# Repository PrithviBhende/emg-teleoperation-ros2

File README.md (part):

# Surface EMG-Based Hand Movement Recognition and Virtual Robotic Hand Teleoperation

An end-to-end cyber-physical pipeline integrating **surface electromyography (sEMG)** bio-signal acquisition, automated **computer vision ground-truth labelling**, **machine learning classification** (evaluating 21 feature-classifier combinations across sets A–G with LDA, SVM, and KNN), and real-time low-latency teleoperation of a 17-DOF **InMoov humanoid robotic hand** in **ROS 2 Humble** and **Gazebo Classic**.

---

## Table of Contents
1. [System Architecture & Dataflow](#1-system-architecture--dataflow)
2. [Hardware Devices & Sensor Configuration](#2-hardware-devices--sensor-configuration)
3. [Custom 6-Channel sEMG Acquisition Hardware (ADS1296)](#3-custom-6-channel-semg-acquisition-hardware-ads1296)
4. [Interactive Graphical User Interface (GUI) Walkthrough](#4-interactive-graphical-user-interface-gui-walkthrough)
5. [Signal Processing, Feature Sets (A to G) & ML Models](#5-signal-processing-feature-sets-a-to-g--ml-models)
6. [ROS 2 & Gazebo Virtual Robotic Hand Simulation](#6-ros-2--gazebo-virtual-robotic-hand-simulation)
7. [Experimental Results & Benchmark Performance](#7-experimental-results--benchmark-performance)
   - [Master Benchmark Evaluation Table](#master-benchmark-evaluation-table)
   - [Waveform Characteristics (All 8 Gestures)](#waveform-characteristics)
   - [Training Results & Graphical Representations (`results/training_results/`)](#-training-results--graphical-representations-directory)
8. [Step-by-Step Guide: How to Make It Work](#8-step-by-step-guide-how-to-make-it-work)
9. [Relative Repositories, Documentation & References](#9-relative-repositories-documentation--references)

---

## 1. System Architecture & Dataflow

The system bridges biological neuromuscular intent to virtual robotic actuation through a synchronized multi-stage pipeline:

```mermaid
flowchart LR
    A["Forearm Muscle Flexion"] --> B["sEMG Electrodes + BioAmp Shield"]
    B --> C["Arduino Due (2 kHz 12-bit ADC)"]
    C -->|"Binary Stream: EMG1 Packet + CRC32"| D["Windows Desktop GUI Application"]
    E["Monocular RGB Webcam"] -->|"MediaPipe Hand Landmarker"| D
    D --> F["Windowing (250 ms, 50 ms hop)<br/>Feature Extraction (Sets A–G)"]
    F --> G["Classifier Inference<br/>(LDA / SVM / KNN)"]
    G --> H["Majority Vote & Rejection Gate<br/>(Threshold >= 60%)"]
    H -->|"TCP Socket (localhost:9996)"| I["WSL 2: ros2_gazebo_server"]
    I -->|"/finger_position_controller/commands"| J["Gazebo: InMoov 17-DOF Hand"]
```

1. **Neuromuscular Sensing**: Surface electrical potentials generated during muscle contractions on the forearm are captured by Ag/AgCl differential electrodes.
2. **Signal Conditioning & Digitization**: The analogue signal is band-pass filtered (72–720 Hz) and amplified by an Upside Down Labs Muscle BioAmp Shield v0.3, then sampled by an Arduino Due 12-bit ADC at a continuous **2,000 Hz**.
3. **High-Speed Serial Streaming**: Data is packed into custom framed binary packets (`EMG1` protocol, 26-byte header, 32-sample payload, CRC32 checksum) and sent via Native USB serial to the Windows host.
4. **Automated Vision-Guided Labeling**: A synchronized camera feed processes hand gestures using Google MediaPipe Hand Landmarker, computing 3D geometric finger joint angles to generate objective reference labels during training.
5. **Feature Extraction & Multi-Model Inference**: Overlapping 250 ms windows (50 ms hop) extract time-domain and time-frequency spectral features (Sets A through G). Predictions are computed across Linear Discriminant Analysis (LDA), Support Vector Machine (SVM), and K-Nearest Neighbors (KNN).
6. **Cross-Platform Teleoperation Bridge**: Accepted gesture commands are transmitted over a high-speed TCP socket (`localhost:9996`) to a ROS 2 bridge node running inside WSL 2 Ubuntu 22.04.
7. **Virtual Actuation**: The ROS 2 bridge node translates gesture tokens into 17 target joint angles published to `/finger_position_controller/commands`, driving the simulated InMoov robotic hand in Gazebo Classic in real time.

---

## 2. Hardware Devices & Sensor Configuration

### Single-Channel Benchmarking Platform
* **Microcontroller**: Arduino Due featuring an Atmel/Microchip SAM3X8E 32-bit ARM Cortex-M3 processor clocked at 84 MHz.
  * Internal 12-bit Analog-to-Digital Converter (`0–4095` counts).
  * Hardware timer interrupt-driven sampling at exact 2,000 samples/second.
  * Native USB CDC communication at full bus speed (exceeding standard 115200 baud UART bandwidth constraints).
* **Bio-Potential Amplifier**: Upside Down Labs Muscle BioAmp Shield v0.3.
  * Analogue front-end instrumentation amplifier with differential gain $A_v \approx 1000$.
  * Analogue bandpass filter: $72\text{ Hz} - 720\text{ Hz}$.
  * Power supply: 5.0 V rail derived from Arduino Due 5V pin.
* **Safety & Voltage Conditioning**:
  * **Critical Electrical Constraint**: The Arduino Due SAM3X8E ADC pin A0 is strictly 3.3 V tolerant (`0 – 3.3 V`). Feeding raw 5 V output from the shield risks permanent pin damage.
  * A passive voltage divider and protection network ensures voltage peaks never exceed the 3.3 V threshold under full muscle contraction.
* **Electrodes**:
  * Standard clinical disposable Ag/AgCl hydrogel pre-gelled surface electrodes (24 mm diameter).
  * Placed in a bipolar arrangement along the muscle belly of the *Flexor Digitorum Superficialis* (FDS) and *Flexor Carpi Radialis* (FCR) on the anterior forearm.
  * Ground / reference electrode placed on a neutral bony landmark: the olecranon process of the elbow.

---

## 3. Custom 6-Channel sEMG Acquisition Hardware (ADS1296)

To scale from single-channel discrimination to simultaneous multi-finger gesture decoding, a dedicated **6-channel bio-potential acquisition carrier board** was designed in KiCad.

### Key Architectural Specifications
* **Analog Front-End (AFE)**: Texas Instruments **ADS1296** (6-channel, 24-bit simultaneous sampling delta-sigma ADC with programmable gain amplifiers, PGA = 1 to 12).
* **Sampling Throughput**: Target 4,000 samples/second per channel across 6 simultaneous differential channels (24-bit frame = 21 bytes per sample, 84 kB/s raw stream).
* **Host Controller**: Removable **Waveshare ESP32-S3-Tiny** dual-core Xtensa LX7 MCU mounted via dual 1x9 female header sockets (2.54 mm pitch, 15.24 mm row spacing).
* **Board Dimensions**: 100 mm x 80 mm, 4-layer FR4 stackup, 1.6 mm thickness.
* **Power Supply**:
  * Battery branch input: 5.0 V regulated via J1.
  * Analog rail: Texas Instruments **LP5907** ultra-low-noise 3.0 V linear regulator (sub-10 µV RMS output noise, 250 mA rating).
  * Digital rail: 3.3 V supplied by the ESP32-S3 module.

### PCB Layer Stackup
| Layer | Name | Type | Description |
|:---:|:---|:---:|:---|
| **L1** | F.Cu | Top Signal | Surface-mount components (109 footprints), high-frequency SPI bus, RF antenna keepout |
| **L2** | In1.Cu | Ground Plane | Solid, uninterrupted GND reference return plane across entire board |
| **L3** | In2.Cu | Power Plane | Clean analog AVDD (3.0 V) copper pour, isolated digital power routing |
| **L4** | B.Cu | Bottom Signal | Critical return paths, plus underside decoupling capacitors (C14, C27, R21, C23) |

### Hierarchical Schematic Architecture

The KiCad project is structured across seven modular hierarchical sheets:

#### Sheet 01: Root Hierarchical Architecture
Orchestrates global inter-sheet busses, power rails, differential analog input channels, SPI command lines, and ground isolation.

#### Sheet 02: Power Management & Low-Noise Decoupling
Houses the TI LP5907 3.0V low-dropout regulator, bulk input tantalum capacitors, LC filter beads, and localized ceramic decoupling capacitors ($10\text{ }\mu\text{F} \parallel 0.1\text{ }\mu\text{F}$) positioned immediately adjacent to power pins.

#### Sheet 03: ADS1296 Bio-Potential Core & Pin Mapping
Contains the central 64-pin TQFP ADS1296 analog front-end, internal reference generation ($V_{REF} = 2.42\text{ V}$), charge pump decoupling (VCAP1, VCAP2, VCAP3, VCAP4), clock oscillators, and digital SPI lines.

#### Sheets 04 & 05: Electrode Input Protection & Anti-Aliasing (CH1–CH3 & CH4–CH6)
Provides identical differential input conditioning for all 6 channels:
* Differential low-pass filter: $R_{in1} = 22\text{ k}\Omega$, $R_{in2} = 24.9\text{ k}\Omega$, $C_{diff} = 1.8\text{ nF}$ (differential cut-off frequency $f_c \approx 942.6\text{ Hz}$).
* Common-mode RF filtering: $C_{cm} = 47\text{ pF}$ to analog ground.
* Transient overvoltage clamping: Texas Instruments **TPD4E001** 4-channel low-capacitance ESD protection diode arrays.

#### Sheet 06: Active Body Bias & Driven-Right-Leg (RLD) Feedback
Features an inverting operational amplifier circuit deriving the common-mode potential from selected channel inputs, inverting it, and actively driving it back to the body via a dedicated reference electrode (J8). This dynamically suppresses 50 Hz/60 Hz mains interference.

#### Sheet 07: Waveshare ESP32-S3-Tiny Carrier Socket & SPI Interface
Defines the dual 1x9 socket interface mapping the ESP32-S3 GPIO pins to the ADS1296 SPI lines.

| Signal | ADS1296 Pin | ESP32-S3 GPIO | Header Contact | Function |
|:---|:---:|:---:|:---:|:---|
| **CS** | 39 | **GPIO 2** | Pin 5 | Chip Select (Active Low) |
| **MOSI (DIN)** | 43 | **GPIO 1** | Pin 4 | SPI Master-Out Slave-In |
| **SCLK** | 40 | **GPIO 12** | Pin 18 | SPI Serial Clock (up to 20 MHz) |
| **MISO (DOUT)** | 42 | **GPIO 13** | Pin 17 | SPI Master-In Slave-Out |
| **DRDY** | 47 | **GPIO 14** | Pin 16 | Data Ready Interrupt (Active Low) |
| **START** | 38 | **GPIO 15** | Pin 15 | Conversion Start Trigger |
| **PWDN_N** | 33 | **GPIO 16** | Pin 14 | Hardware Power-Down (Active Low) |
| **RESET_N** | 34 | **GPIO 17** | Pin 13 | Hardware Reset (Active Low) |

---

## 4. Interactive Graphical User Interface (GUI) Walkthrough

The Windows desktop application provides a complete control station for data acquisition, visual verification, machine learning model comparison, and real-time robotic teleoperation.

### Control & Button Breakdown

#### 1. Top Control Bar (Device Connection & Setup)
* **`Subject` (Text Entry)**: Sets the subject identifier (e.g. `P01`). All captured raw files, models, and metadata are saved under isolated subject directories (`data/<Subject>/`).
* **`Placement` (Text Entry)**: Sets the electrode placement index (e.g. `P1` to `P8`). Moving electrodes creates a new folder to prevent cross-placement data contamination.
* **`COM port` (Dropdown / Entry)**: Specifies the active serial COM port for the Arduino Due (e.g. `COM7`).
* **`List ports` (Button)**: Enumerates all active Windows serial devices, distinguishing Native USB endpoints from standard programming ports.
* **`Connect Due` (Button)**: Opens the serial connection, executes the safety handshake, queries firmware version, and starts the 2,000 Hz `EMG1` packet stream.
* **`Camera #` (Dropdown)**: Selects the Windows camera device index (0, 1, 2) to accommodate multiple webcams or DroidCam devices.
* **`Camera` (Toggle Button)**: Powers on/off the OpenCV webcam stream and initiates the MediaPipe Hand Landmarker visual tracking thread.
* **`Settings / timings` (Button)**: Opens the configuration modal to inspect or edit window lengths (default 1.2 s), pre/post-trigger intervals, filter poles, and rejection thresholds.
* **`New session` (Button)**: Generates a new session timestamp directory to maintain clean separation between recording blocks.

#### 2. Protocol & Acquisition Bar
* **`Training block / Verify reference` (Dropdown)**: Selects the active target gesture class: `rest`, `thumb`, `index`, `middle`, `ring`, `little`, `pinch`, `fist`.
* **`Repeat Train` (Checkbox)**: When checked, the application automatically rearms for the next repetition as soon as the previous trial is reviewed, enabling rapid batch training.
* **`Start Train` (Button)**: Arms the system for movement recording. Captures 1.0 s before and 1.5 s after the detected camera event. Opens an interactive review window where the user can inspect the raw EMG waveform, drag a 1.2 s selection window, and confirm the trial.
* **`Verify` (Button)**: Development verification mode. Extracts features and computes live model predictions against the chosen reference gesture to test model responsiveness.
* **`Test (Enter)` (Button)**: Official held-out test protocol. Captures a live movement, prompts the user to verify the camera label first, extracts features, runs autonomous EMG classification, and logs the result to `test_results.json`.
* **`Series Test` (Button)**: Multi-repetition test suite. Records multiple sequential movements, slides adjustable 1.2 s windows, and computes aggregate classification accuracy across repetitions.
* **`Capture relaxed rest` (Button)**: Manually captures baseline rest EMG with a neutral hand, guaranteeing unbiased resting baseline data.
* **`Stop` (Button)**: Immediately halts any running acquisition, disarms repeat training, or cancels ongoing data capture.

#### 3. Analysis, Export & Model Management
* **`Train / compare models` (Button)**: Opens the training manager. Fits all **21 model combinations** (Feature Sets A through G $\times$ Classifiers LDA, SVM, KNN) using 3-fold cross-validation on held-out trials, logs confusion matrices, and selects the champion model.
* **`Load latest models` (Button)**: Instantly reloads the most recently trained `.joblib` model pipeline and JSON validation parameters without retraining.
* **`Export Excel + plots` (Button)**: Exports a structured multi-sheet Excel workbook containing trial metadata, windowed feature matrices, model comparison tables, and generates matplotlib waveform figures.
* **`Show results` (Button)**: Displays a comprehensive modal showing held-out test accuracy, per-class recall, confusion matrices, macro F1 score, and coverage.
* **`Manual Test: Start` (Button)**: Runs a camera-free test session. Allows the user to click Start, perform any gesture, click Stop, slide the 1.2 s green inspection window over the signal, and view the predicted gesture.
* **`Delete last recording` (Button)**: Reversible deletion button that removes the most recent trial from disk if a false start, twitch, or improper movement occurred.
* **`Analysis band-pass` (Checkbox)**: Toggles an optional digital 4th-order Butterworth bandpass filter (70–450 Hz) for visual analysis without modifying the recorded raw ADC counts.
* **`50 Hz notch` (Checkbox)**: Enables/disables a digital 2nd-order IIR notch filter ($Q=30$) at 50 Hz to attenuate powerline hum in noisy environments.

#### 4. Live Visual Displays
* **Scrolling Oscilloscope**: Displays real-time EMG signals:
  * Blue trace: Raw, unadulterated ADC counts (`0 – 4095`).
  * Orange trace: Filtered analysis copy with DC bias removed.
* **Camera Preview Area**: Renders the live webcam feed overlaid with 21 MediaPipe hand landmarks, indicating whether each digit is bent (B), straight (S), or uncertain (U).
* **Virtual Robotic Hand Bar Indicators**: 5 vertical progress bars representing `thumb`, `index`, `middle`, `ring`, and `little` finger positions. Teleoperation commands dynamically flex the simulated bars and display active posture (e.g. `Simulation: rest`, `Simulation: index`).
* **Console Status Pane**: Displays real-time operational messages, including TCP bridge connection (`[GazeboBridge] Connected to ROS 2 Gazebo TCP server (port 9996)`).
* **Safety Advisory Banner**: Permanent hardware warning: `DUE A0: 0 - 3.3 V ONLY. No automatic 5 V conversion.`

---

## 5. Signal Processing, Feature Sets (A to G) & ML Models

### 5.1 Windowing & Preprocessing
* **Sample Rate**: $f_s = 2000\text{ Hz}$ ($T_s = 0.5\text{ ms}$).
* **Window Duration**: $W = 250\text{ ms}$ (500 samples).
* **Hop Interval**: $\Delta t = 50\text{ ms}$ (100 samples), creating a **75% overlap** between adjacent windows.
* **Windows per Trial**: For each reviewed 1.20 s trial, exactly **20 overlapping windows** are extracted.
* **Mean Centering**: Each window is centered by subtracting its mean ($x_i - \bar{x}$) to eliminate DC bias while preserving raw sample archives.

### 5.2 Mathematical Formulations for Feature Sets A to G

| Set | Code | Dimensions | Mathematical Formulation | Description |
|:---:|:---|:---:|:---|:---|
| **A** | `A_RMS` | 1 | $\text{RMS} = \sqrt{\frac{1}{N} \sum_{i=1}^N x_i^2}$ | Root Mean Square; proportional to muscle contraction force and motor unit recruitment. |
| **B** | `B_MAV` | 1 | $\text{MAV} = \frac{1}{N} \sum_{i=1}^N \|x_i\|$ | Mean Absolute Value; robust statistical measure of bio-signal amplitude. |
| **C** | `C_WL` | 1 | $\text{WL} = \sum_{i=1}^{N-1} \|x_{i+1} - x_i\|$ | Waveform Length; cumulative length of the waveform over the window, reflecting amplitude, frequency, and duration. |
| **D** | `D_TD4` | 4 | $[\text{MAV}, \text{WL}, \text{ZC}, \text{SSC}]^T$ | Hudgins' classic 4 time-domain features.<br/>• **Zero Crossings (ZC)**: Sign changes exceeding threshold $\epsilon = 3$ ADC counts.<br/>• **Slope Sign Changes (SSC)**: Extrema $(x_i - x_{i-1})(x_i - x_{i+1}) \ge \epsilon$. |
| **E** | `E_ALL5` | 5 | $[\text{RMS}, \text{MAV}, \text{WL}, \text{ZC}, \text{SSC}]^T$ | Extended time-domain feature vector combining amplitude power and frequency estimators. |
| **F** | `F_MAV_MAX_MIN` | 3 | $[\text{MAV}, \max(x), \min(x)]^T$ | Extreme amplitude features sensitive to burst transients during rapid finger flexion. |
| **G** | `G_TF8` | 8 | $P_k = \log\left(1 + \sum_{f \in B_k} \|X(f)\|^2\right)$ | **Time-Frequency Spectral Log Power**: Computes FFT power in 4 physiological sub-bands ($20–80$, $80–150$, $150–250$, $250–450\text{ Hz}$) separately over the **early half** ($0–125\text{ ms}$) and **late half** ($125–250\text{ ms}$) of the window ($4\times 2 = 8\text{ features}$). |

### 5.3 Machine Learning Classifiers
All models are evaluated within a `scikit-learn` pipeline with a fitted `StandardScaler` to normalize features:
1. **Linear Discriminant Analysis (LDA)**:
   * Solver: Least squares (`lsqr`) with automated Ledoit-Wolf shrinkage (`shrinkage='auto'`).
   * Finds a linear combination of features that maximizes the ratio of between-class variance to within-class variance.
2. **Support Vector Machine (SVM)**:
   * Kernel: Radial Basis Function (RBF) kernel: $K(x, x') = \exp(-\gamma \|x - x'\|^2)$.
   * Regularization parameter: $C = 1.0$, $\gamma = \text{'scale'}$.
3. **K-Nearest Neighbors (KNN)**:
   * Neighborhood size: $k = 5$.
   * Weighting: Inverse Euclidean distance ($w_i = 1 / d(x, x_i)$), giving closer training examples higher influence.

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
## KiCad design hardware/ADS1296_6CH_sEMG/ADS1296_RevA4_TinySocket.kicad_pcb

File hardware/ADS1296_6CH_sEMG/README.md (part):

# A4 TinySocket CapFix - corrected local capacitor and RLD placement

Open ADS1296_RevA4_TinySocket.kicad_pro **inside this CapFix folder** in KiCad 10.0.3 or newer. This is a separate revision based on the user's saved A4 board. The original A4 board and the A3 project are untouched.

The six requested placement limits have been rechecked numerically on the final saved PCB. See [PLACEMENT_RESULTS.md](PLACEMENT_RESULTS.md) for the measurements, trace lengths and assembly changes. The board remains 100 x 80 mm with the same removable Tiny socket. **C14, C27, R21 and its companion C23 now mount on the underside; all other components mount on top.**

## What the small capacitor holes do

The original small 0.3 mm drill holes are plated vias: copper tunnels linking board layers. Most near the bypass capacitors provide short ground-plane returns. Others carry supply or signal connections. They are not mounting holes or connector sockets, and do not require inserting a component. They are retained in this revision.

The MCU attachment now uses larger **1.0 mm finished plated-through-hole targets with 1.8 mm lands** for soldered female sockets. Bare holes alone do not make a reliable removable electrical connection.

## New removable attachment

- Same preassembled **Waveshare ESP32-S3-Tiny, SKU27069**, or **Tiny-Kit SKU27070** including the USB-C adapter and FPC. Not ESP32-S3-MINI-1 or ESP32-S3-Zero.
- **Two 1x9 female sockets** solder onto this carrier, and **two 1x9 male headers** solder to the Tiny's side holes. The Tiny then plugs into the carrier. This requires one-time soldering, not solderless insertion of loose pins into holes.
- **2.54 mm contact pitch; 15.24 mm between row centres**, calculated from the manufacturer's 18 mm body and symmetrical 1.38 mm edge offsets. First row centres are 1.59 mm below the top of the Tiny; the nine contacts span 20.32 mm. The five bottom contacts and underside pads are not used.
- Component A1 is a composite socket/module assembly: its 18 footprint pads represent the two nine-contact female strips. Order both strips and both male headers in addition to the Tiny kit; A1 is not one off-the-shelf 18-pin connector.
- Dimensional reference parts: **2x Harwin M20-7820942 female**, **2x Harwin M20-9990945 male**. The socket is 8.5 mm high and mates with 0.64 mm square pins. Standard equivalents are acceptable only after checking pin size, footprint and housing dimensions; prices and Indian stock were not checked in this revision.
- The header assembly adds height: approximately 11 mm from carrier top to Tiny underside, based on 8.5 mm socket height plus 2.54 mm male-header housing. Confirm actual seating and enclosure clearance.

**Mechanical qualification is still required:** Waveshare's drawing specifies the pitch but not the finished hole diameter/tolerance. We cannot certify that these male pins fit the purchased Tiny without a measurement or vendor confirmation. Do not drill/enlarge its plated holes to force a fit. Print SOCKET_TEMPLATE_1TO1.svg at 100%, check the 10 mm ruler, and compare an actual Tiny before ordering the carrier. Also check that the male-header plastic clears components on the Tiny underside.

**Power off before insertion/removal. These connectors are unkeyed.** Align the Tiny's 5V pad with carrier pad1, towards the antenna/top edge. Reverse insertion or a one-position offset can damage both boards. Support the carrier when inserting/removing; pull both sides evenly without pulling the FPC cable. Add nonconductive mechanical retention for a wearable enclosure, with no metal against the antenna.

## GPIO changes - update firmware

| Signal | A3 GPIO | A4 socket GPIO | Tiny side contact |
|---|---:|---:|---:|
| CS | 10 | **2** | 5 |
| MOSI / ADS DIN | 11 | **1** | 4 |
| SCLK | 12 | 12 | 18 |
| MISO / ADS DOUT | 13 | 13 | 17 |
| DRDY | 14 | 14 | 16 |
| START | 15 | 15 | 15 |
| PWDN_N | 16 | 16 | 14 |
| RESET_N | 17 | 17 | 13 |

GPIO1/2 are available side contacts and avoid the USB/strapping/PSRAM pins. Native USB still travels over the Tiny's supplied FPC to its kit adapter, not through this carrier. This CapFix retains the A4 socket position, GPIO assignments, existing component values and packages. Local analogue/supply/reference/RLD placement and routing have changed to meet the six limits; physical behaviour has not been measured.

Target remains six channels at **4,000 samples/s per channel**: 21-byte ADS frame gives 84,000 bytes/s before framing. Proposed 4 MHz SPI reads the 168-bit frame in 42 us out of a 250 us period. These calculations do not prove lossless acquisition. Firmware and a sustained sequence-counter capture test remain separate work. No firmware is included here.

## Carrier and connections retained

- 100 x 80 mm, four copper layers, 1.6 mm nominal thickness. F.Cu components/signals; In1.Cu ground reference with no routed tracks; In2.Cu analogue AVDD pour and selected signals; B.Cu selected signals and four SMD components. The antenna keepout remains.
- 109 footprints are on top; C14, C27, R21 and C23 are on the underside. This requires two-sided assembly, including soldering the through-hole sockets/connectors from below. Resistors/capacitors remain 0805 or larger. The ADS1296 still needs careful 0.5 mm-pitch TQFP soldering. See both assembly drawings before soldering; underside drawings are mirrored for viewing from below.
- J1: pin1 regulated 5.0-5.25 V, pin2 GND; not a raw Li-ion cell input. No charger. SW1 controls only the battery branch; USB can still power the system.
- J2-J7: respective CH1-CH6 electrode connectors. Pin1=P, pin2=N, pin3=NC. The retained schematic value says SHIELD but pin3 is not connected.
- J8: pin1 bias/RLD output, pin2=NC. Six pairs plus a separate bias use 13 electrodes.
- Tiny supplies digital 3.3 V. LP5907 separately supplies AVDD. Do not parallel regulator outputs or add external 3.3 V to the Tiny output.
- Input network: 22k + 24.9k in each leg and 1.8nF differential capacitor. Ideal RC pole remains 942.6 Hz, not a 20-450 Hz band-pass or mains notch. Later software filtering is separate.
- Reference, VCAP and RLD values are unchanged. RLD starts disabled; verify it on dummy electrode/cable loads before enabling it for recordings. All six requested XY footprint-centre to U1-pad-centre limits now pass. These are placement distances, not copper lengths: underside parts add layer-change vias and board thickness. Each of the five capacitors has a distinct nearby ground via with an explicit short local return.

## Validation and files

Native ERC/DRC, a socket/pin/route audit and a separate six-target measurement check are included. Check VERIFICATION.json, SIX_TARGET_VERIFICATION.json, routed_drc.json and erc.json. CHANGE_AUDIT.json records changes relative to the preserved user-saved A4 board, including restoration of missing C152 to match the schematic. The final PCB SHA256 in the reports identifies the exact checked design. The dimensional template is nominal, not a measured fit test.

ROUTING_TOP/BOTTOM and ASSEMBLY_TOP/BOTTOM are supplied as SVG and PNG. ASSEMBLY_POSITIONS.pos lists component positions and faces. The fabrication_review folder contains newly exported copper, mask, silkscreen, paste and drill files for this exact revision, including the backside SMD layers. PACKAGE_SHA256.json identifies the packaged files.

The schematic_images folder contains all seven schematic sheets as PNG pictures for quick viewing and SVG files for zooming or printing without loss of detail.

The connection_diagrams folder contains three simpler, labelled component-and-wire pictures: main electrode/MCU connections, power and capacitors, and input protection/body bias. These were drawn locally from a fresh schematic netlist and include a connection-check report. Pin positions are rearranged for readability; use the PCB assembly drawings for physical placement.

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
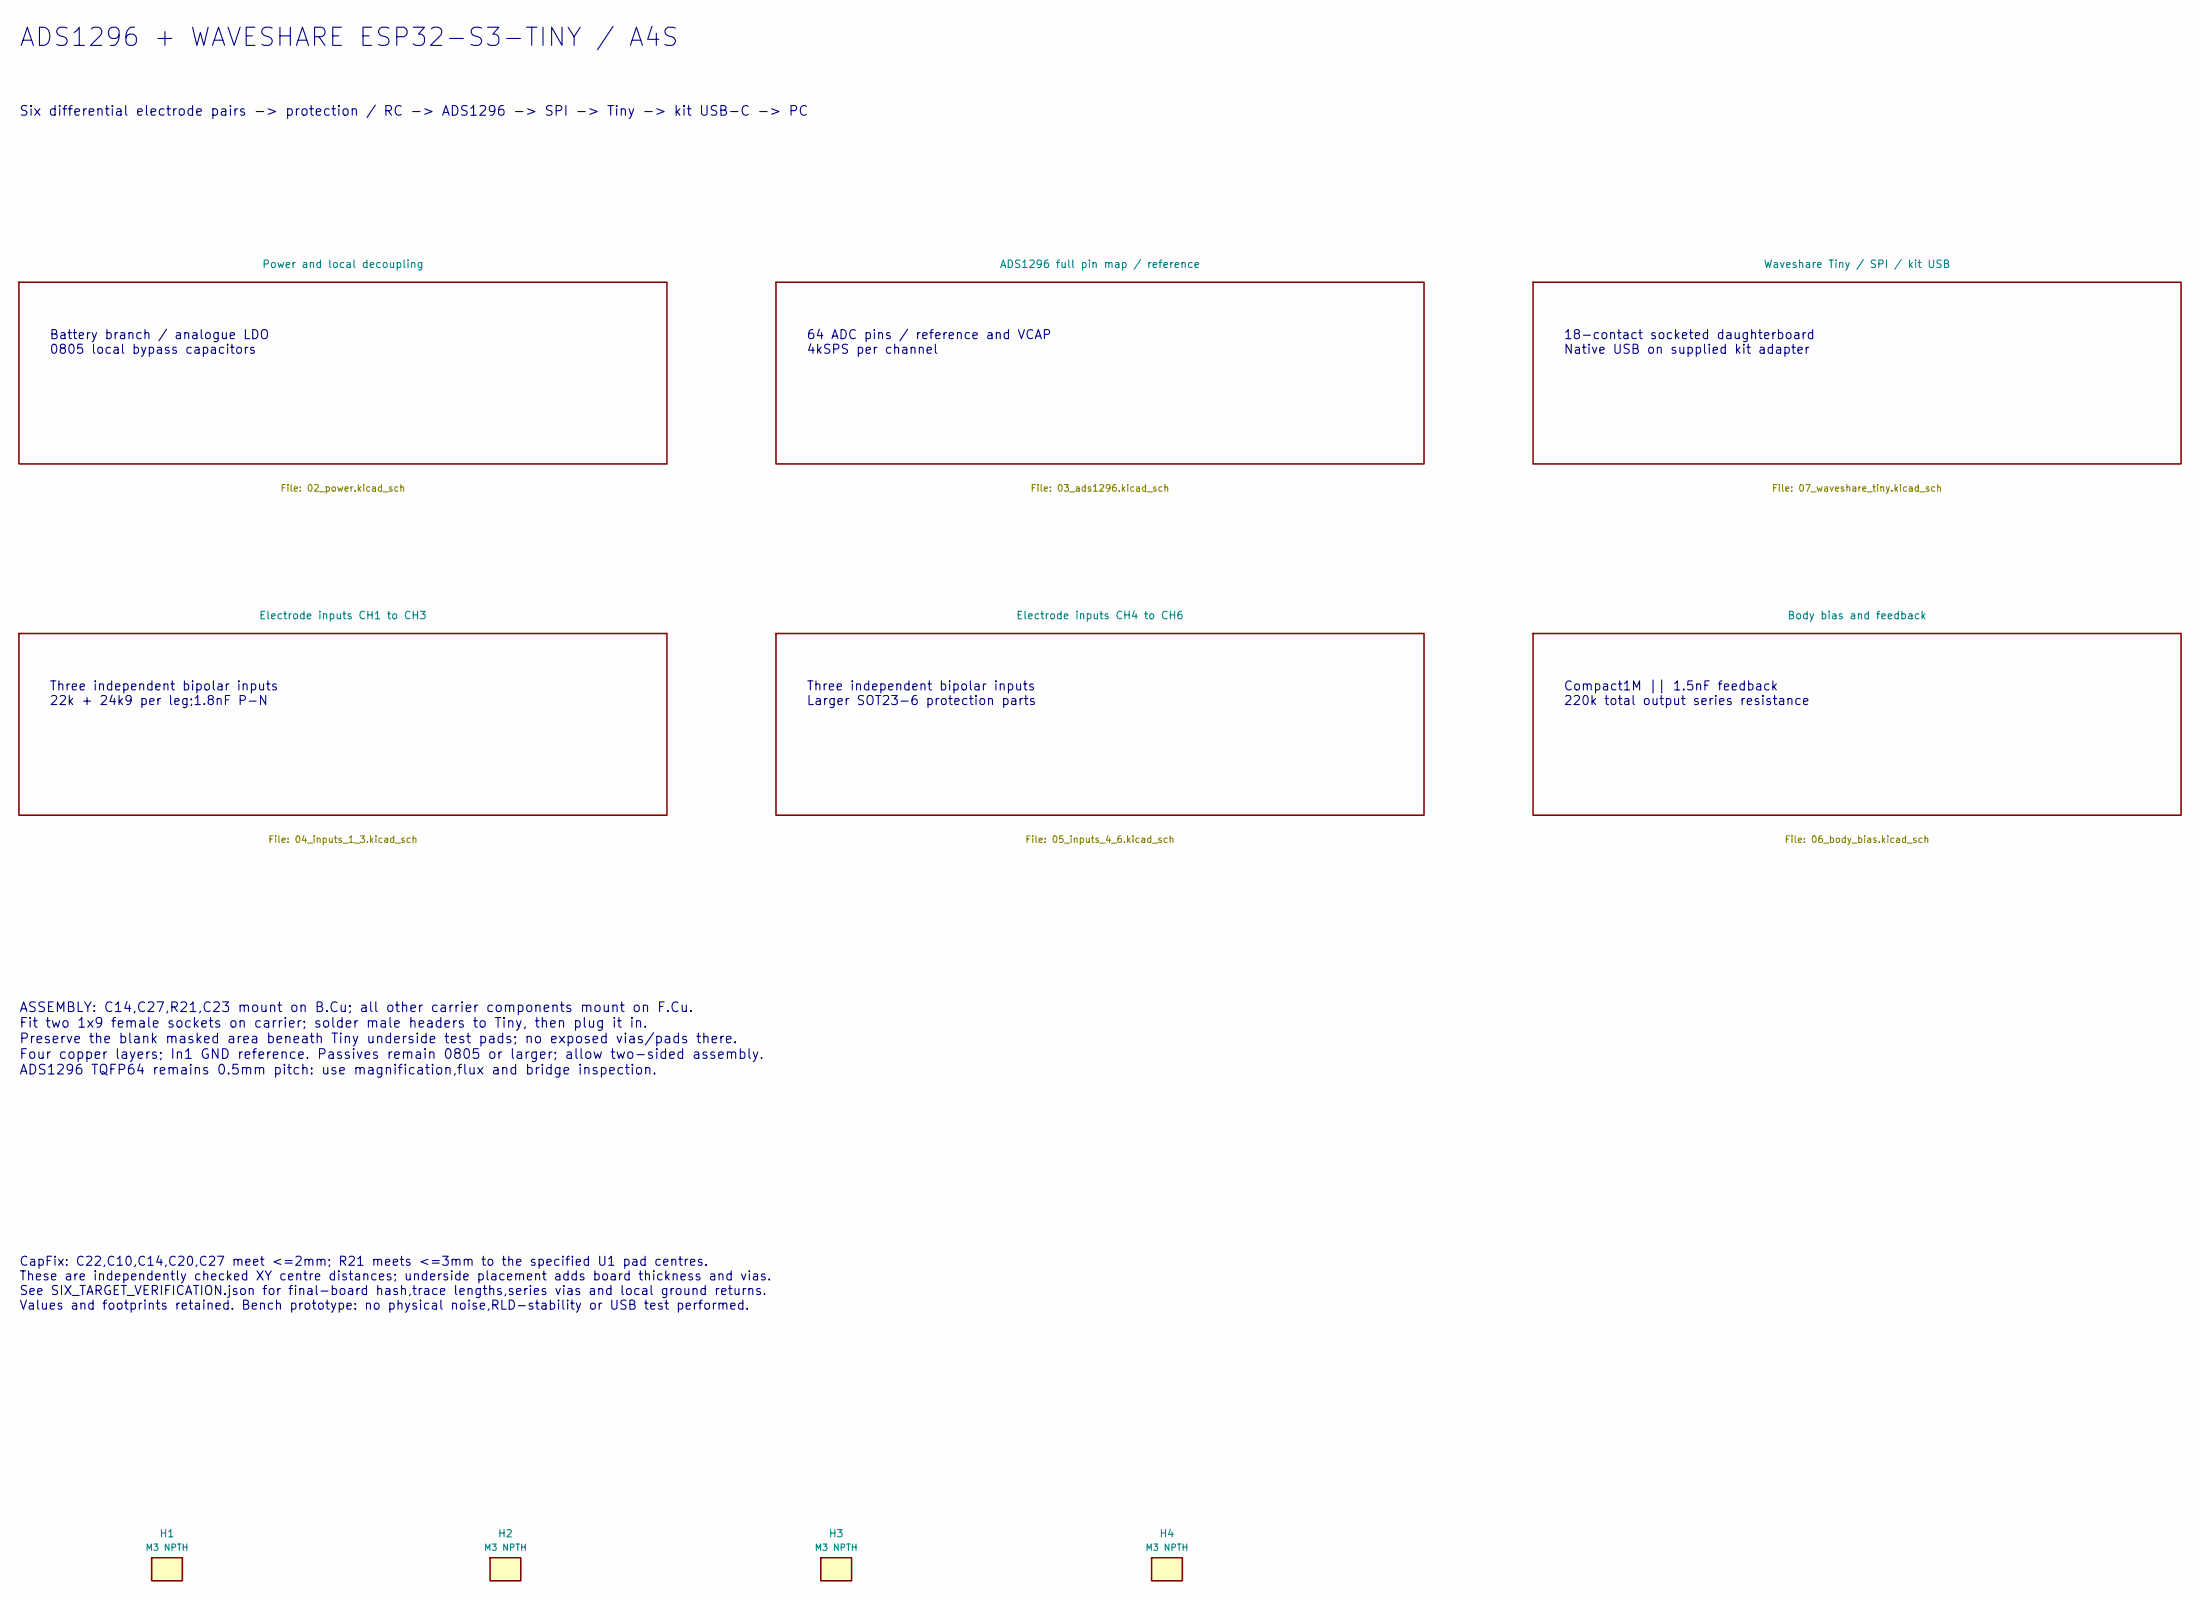
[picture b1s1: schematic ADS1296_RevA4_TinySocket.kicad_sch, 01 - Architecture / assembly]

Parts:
H1, H2, H3, H4: M3 NPTH; MountingHole_3.2mm_M3; MPN M3 nylon screw + spacer

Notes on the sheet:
ADS1296 + WAVESHARE ESP32-S3-TINY / A4S
Six differential electrode pairs -> protection / RC -> ADS1296 -> SPI -> Tiny -> kit USB-C -> PC
Battery branch / analogue LDO 0805 local bypass capacitors
64 ADC pins / reference and VCAP 4kSPS per channel
18-contact socketed daughterboard Native USB on supplied kit adapter
Three independent bipolar inputs 22k + 24k9 per leg;1.8nF P-N
Three independent bipolar inputs Larger SOT23-6 protection parts
Compact1M || 1.5nF feedback 220k total output series resistance
ASSEMBLY: C14,C27,R21,C23 mount on B.Cu; all other carrier components mount on F.Cu. Fit two 1x9 female sockets on carrier; solder male headers to Tiny, then plug it in. Preserve the blank masked area beneath Tiny underside test pads; no exposed vias/pads there. Four copper layers; In1 GND referenc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
CapFix: C22,C10,C14,C20,C27 meet <=2mm; R21 meets <=3mm to the specified U1 pad centres. These are independently checked XY centre distances; underside placement adds board thickness and vias. See SIX_TARGET_VERIFICATION.json for final-board hash,trace lengths,series vias and local ground returns. 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

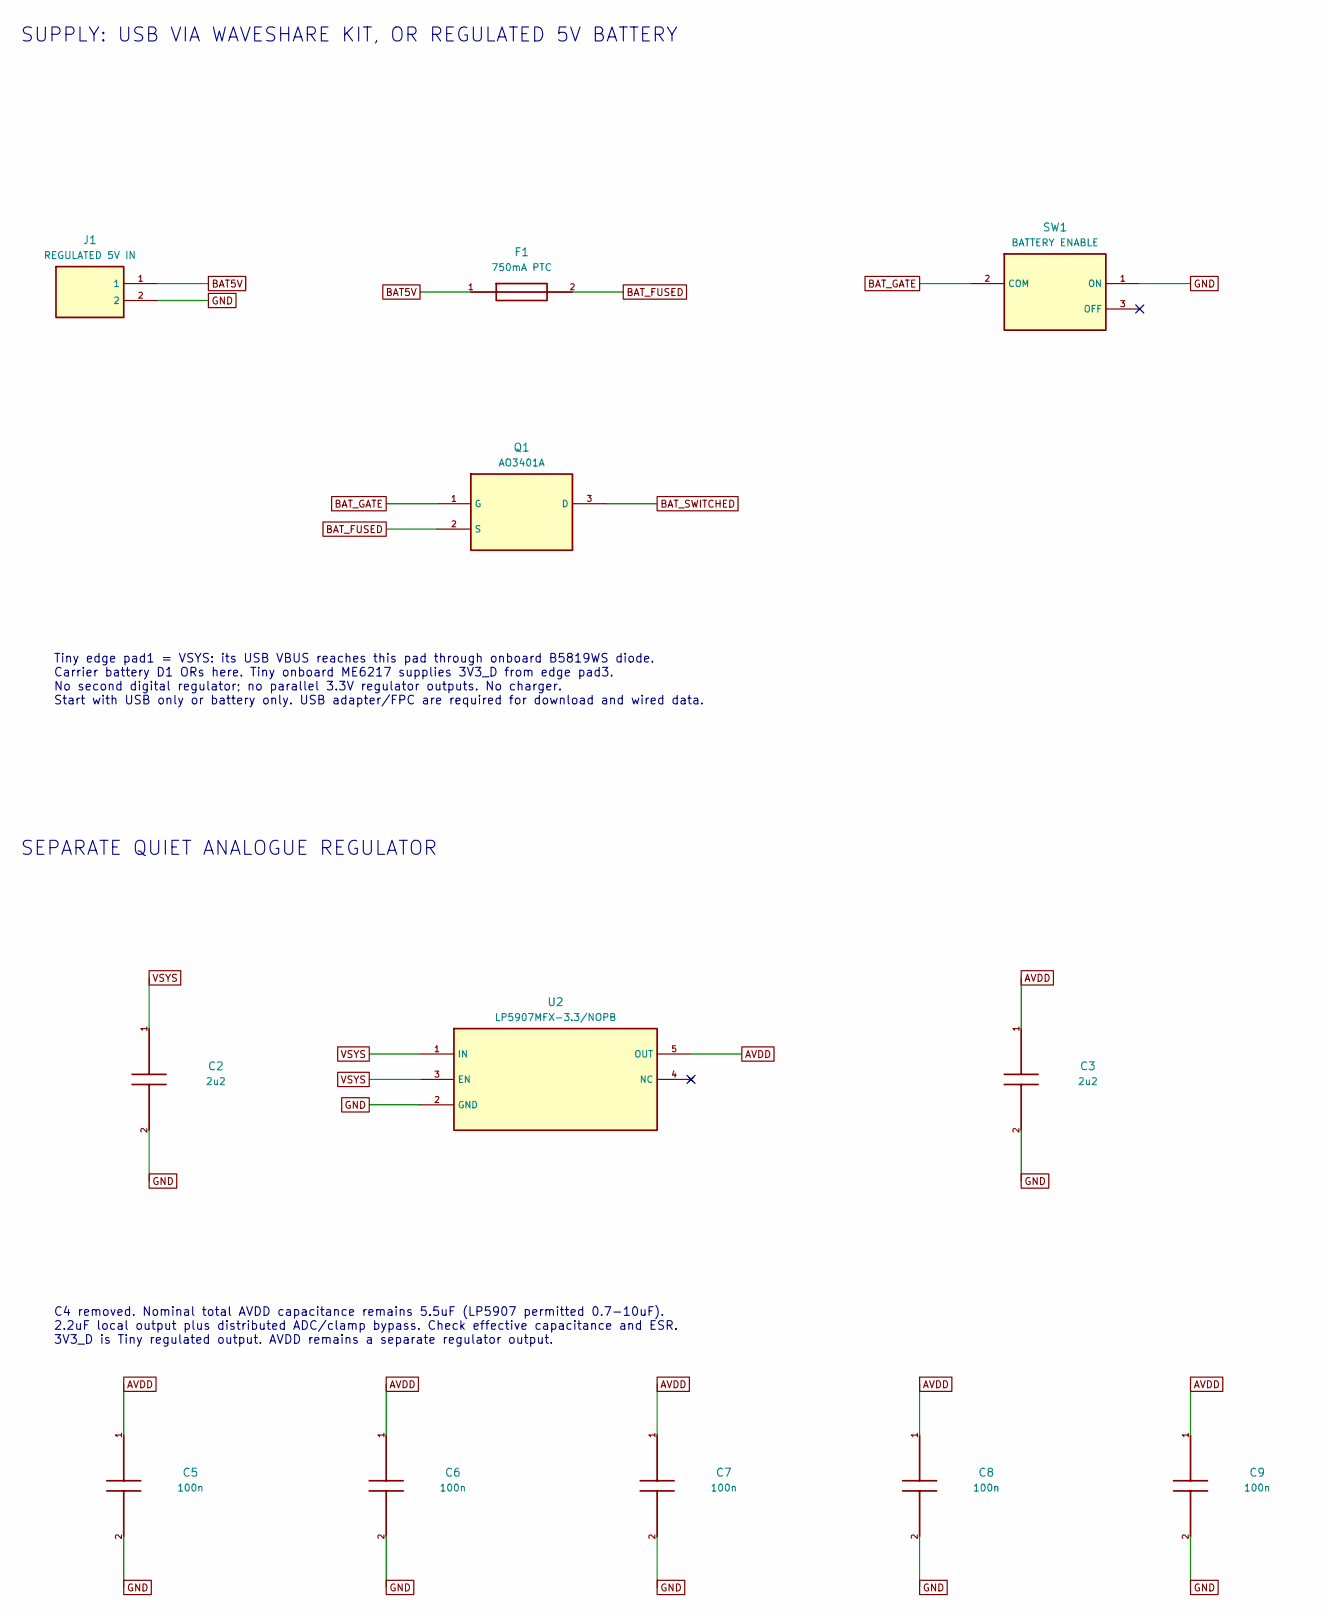
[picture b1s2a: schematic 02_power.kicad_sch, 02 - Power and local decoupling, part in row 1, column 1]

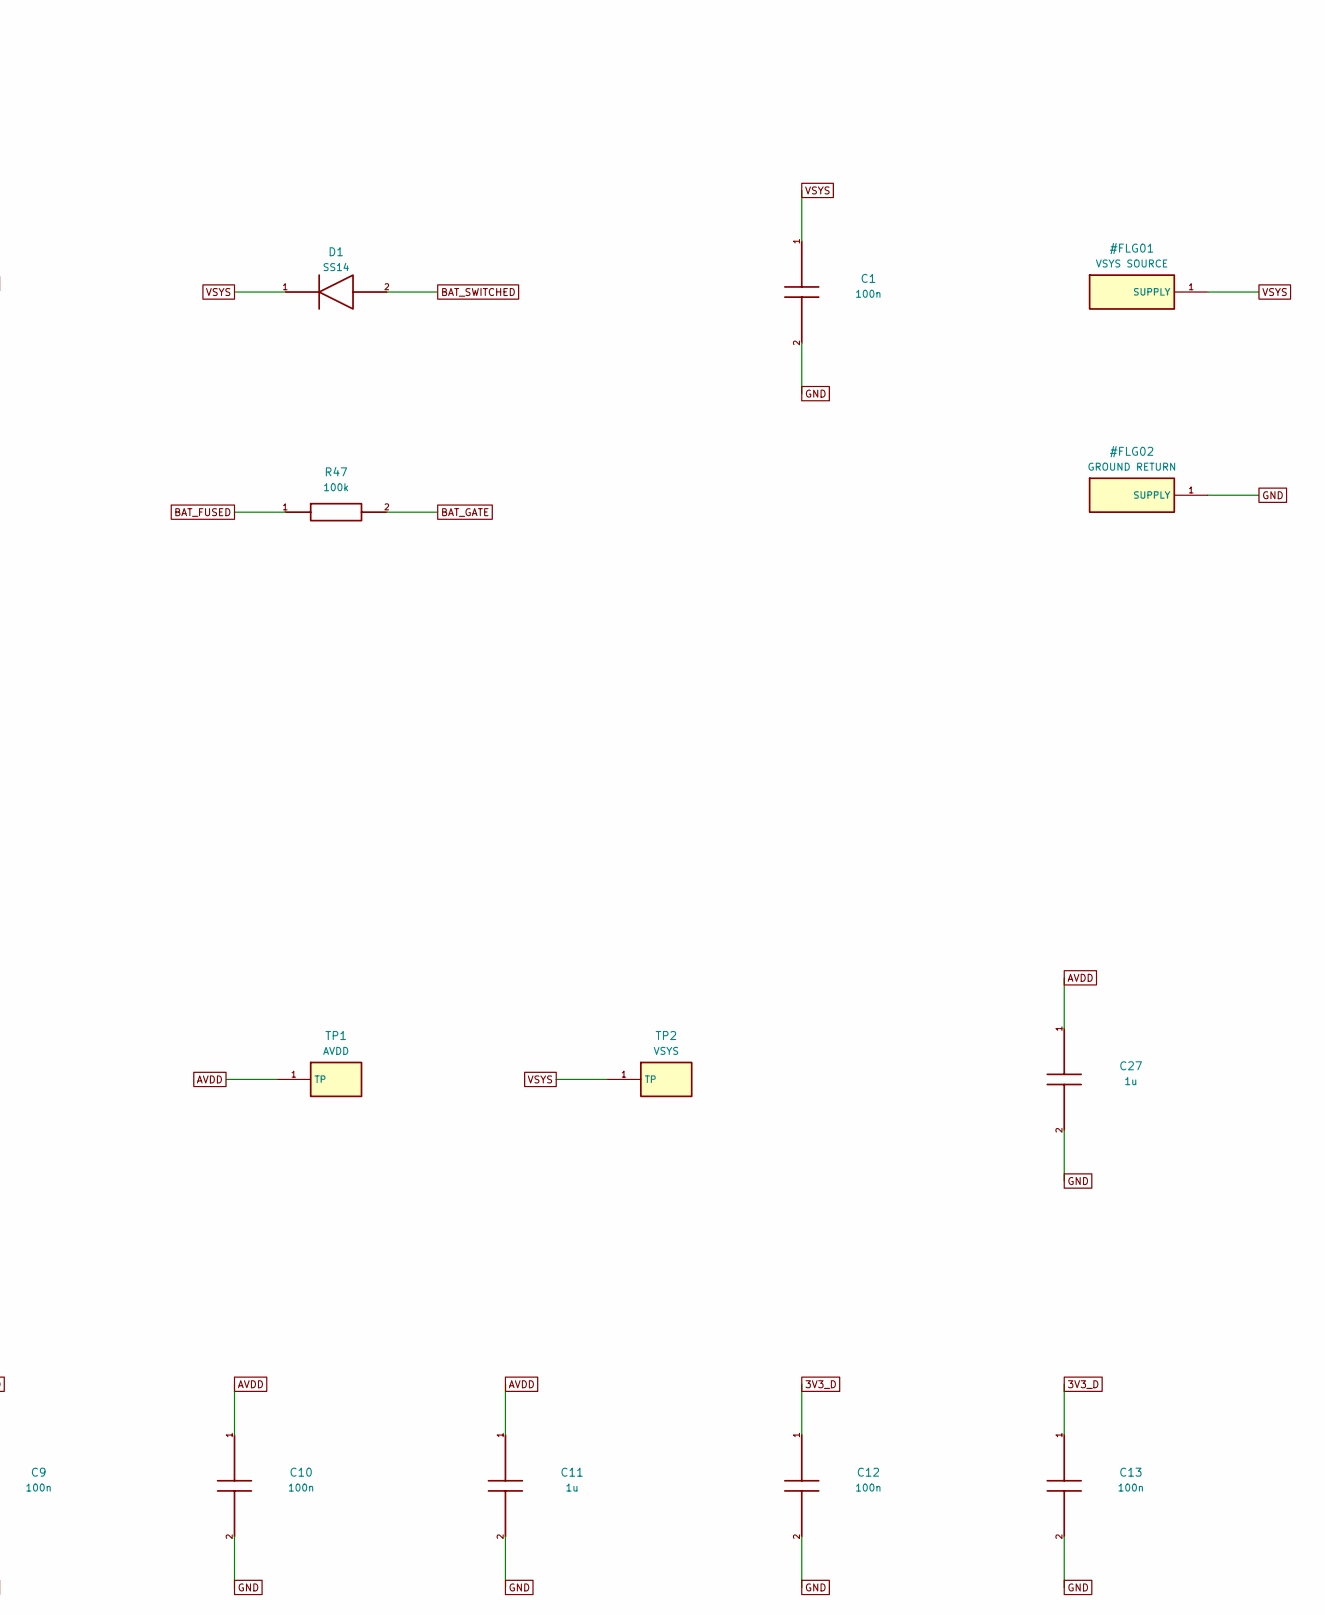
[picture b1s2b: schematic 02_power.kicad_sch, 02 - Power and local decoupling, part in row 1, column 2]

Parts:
C1, C5, C6, C7, C8, C9, C10, C12, C13: 100n; C_0805_2012Metric; MPN C0805C104K4RACTU
C2, C3: 2u2; C_0805_2012Metric; MPN C0805C225K4RACTU
C11, C27: 1u; C_0805_2012Metric; MPN C0805C105K4RACTU
D1: SS14; D_SMA; MPN SS14
F1: 750mA PTC; Fuse_1812_4532Metric; MPN MF-MSMF075-2
J1: REGULATED 5V IN; JST_XH_B2B-XH-A_1x02_P2.50mm_Vertical; MPN B2B-XH-A(LF)(SN)
Q1: AO3401A; SOT-23; MPN AO3401A
R47: 100k; R_0805_2012Metric; MPN RC0805FR-07100KL
SW1: BATTERY ENABLE; SW_SPDT_CK_JS102011SAQN; MPN JS102011SAQN
TP1: AVDD; TestPoint_Pad_D1.5mm
TP2: VSYS; TestPoint_Pad_D1.5mm
U2: LP5907MFX-3.3/NOPB; SOT-23-5; MPN LP5907MFX-3.3/NOPB

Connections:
3V3_D: C12.1, C13.1; also elsewhere on the board
AVDD: C3.1, C5.1, C6.1, C7.1, C8.1, C9.1, C10.1, C11.1, C27.1, TP1.1, U2.5 (OUT); also elsewhere on the board
BAT5V: F1.1, J1.1
BAT_FUSED: F1.2, Q1.2 (S), R47.1
BAT_GATE: Q1.1 (G), R47.2, SW1.2 (COM)
BAT_SWITCHED: D1.2, Q1.3 (D)
GND: C1.2, C2.2, C3.2, C5.2, C6.2, C7.2, C8.2, C9.2, C10.2, C11.2, C12.2, C13.2, C27.2, J1.2, SW1.1 (ON), U2.2 (GND); also elsewhere on the board
VSYS: C1.1, C2.1, D1.1, TP2.1, U2.1 (IN), U2.3 (EN); also elsewhere on the board

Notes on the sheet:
SUPPLY: USB VIA WAVESHARE KIT, OR REGULATED 5V BATTERY
Tiny edge pad1 = VSYS: its USB VBUS reaches this pad through onboard B5819WS diode. Carrier battery D1 ORs here. Tiny onboard ME6217 supplies 3V3_D from edge pad3. No second digital regulator; no parallel 3.3V regulator outputs. No charger. Start with USB only or battery only. USB adapter/FPC are r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
SEPARATE QUIET ANALOGUE REGULATOR
C4 removed. Nominal total AVDD capacitance remains 5.5uF (LP5907 permitted 0.7-10uF). 2.2uF local output plus distributed ADC/clamp bypass. Check effective capacitance and ESR. 3V3_D is Tiny regulated output. AVDD remains a separate regulator output.

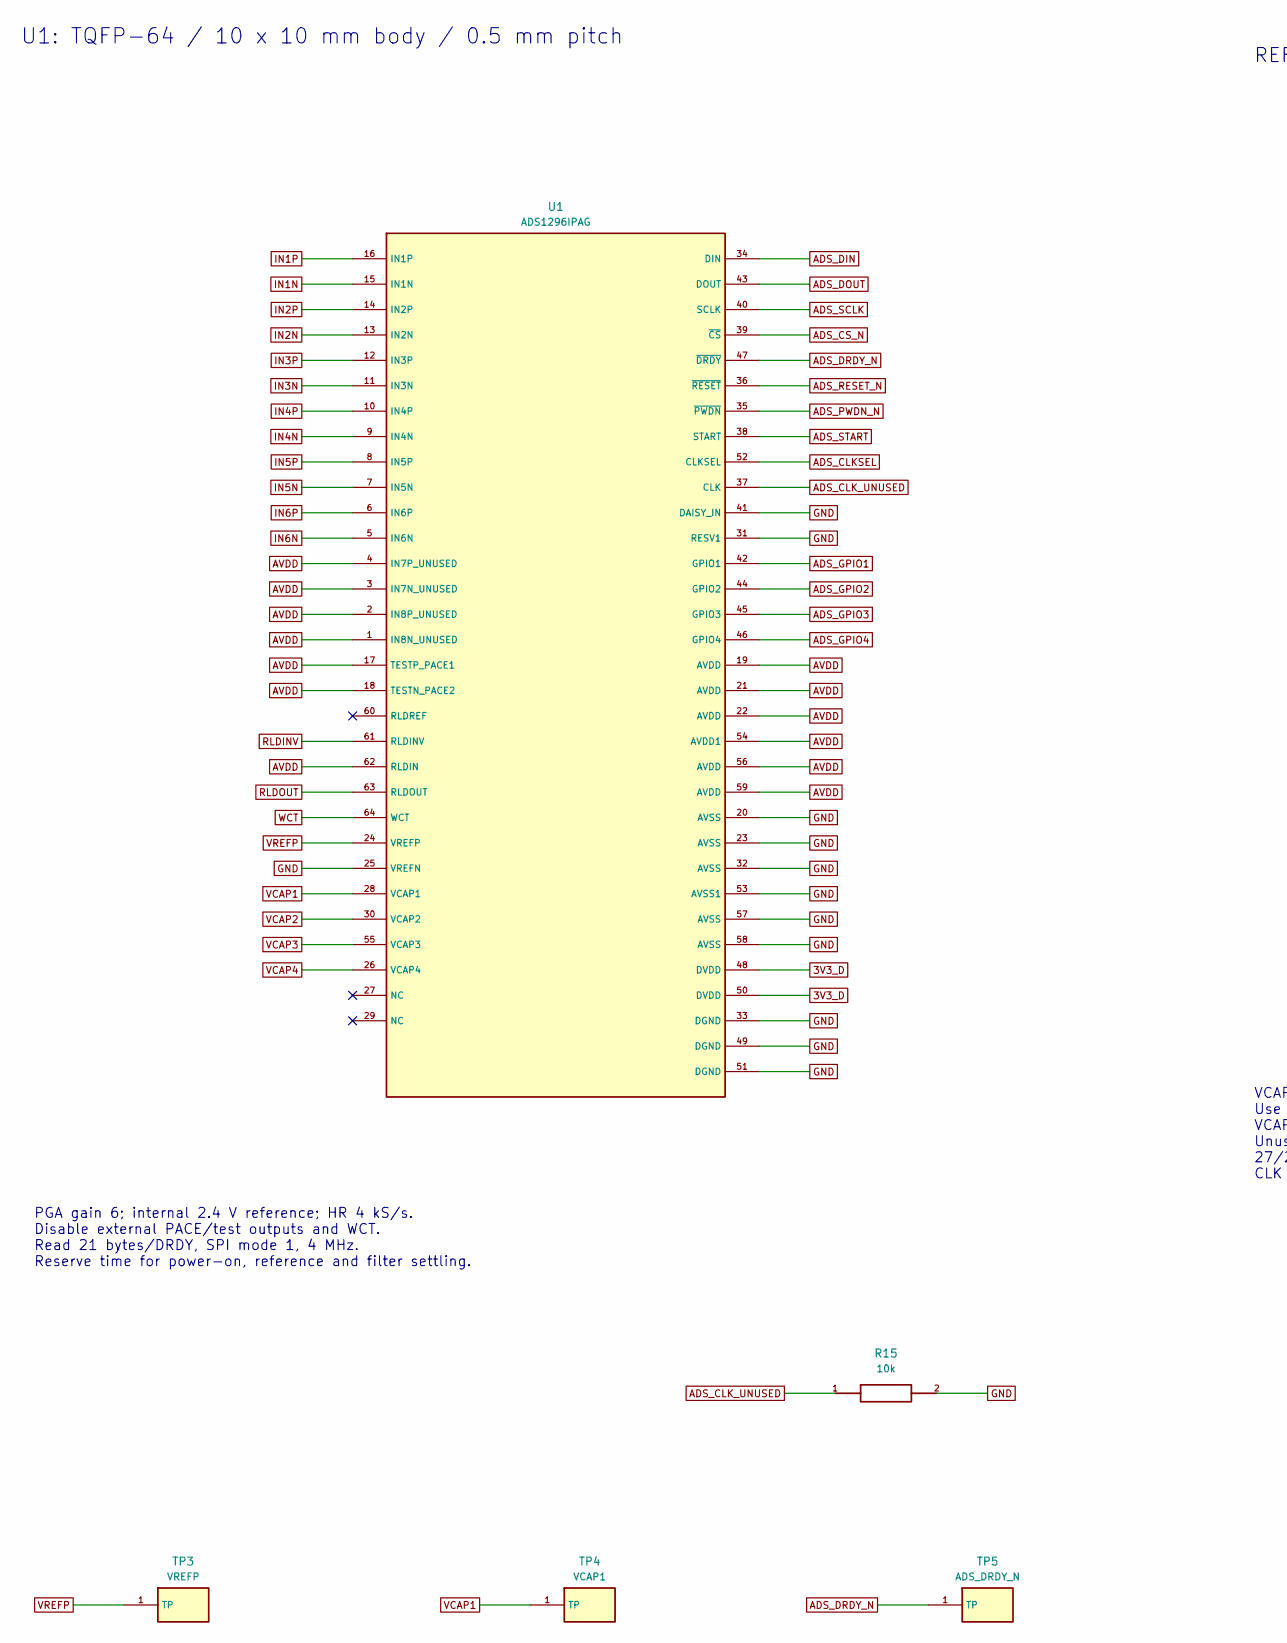
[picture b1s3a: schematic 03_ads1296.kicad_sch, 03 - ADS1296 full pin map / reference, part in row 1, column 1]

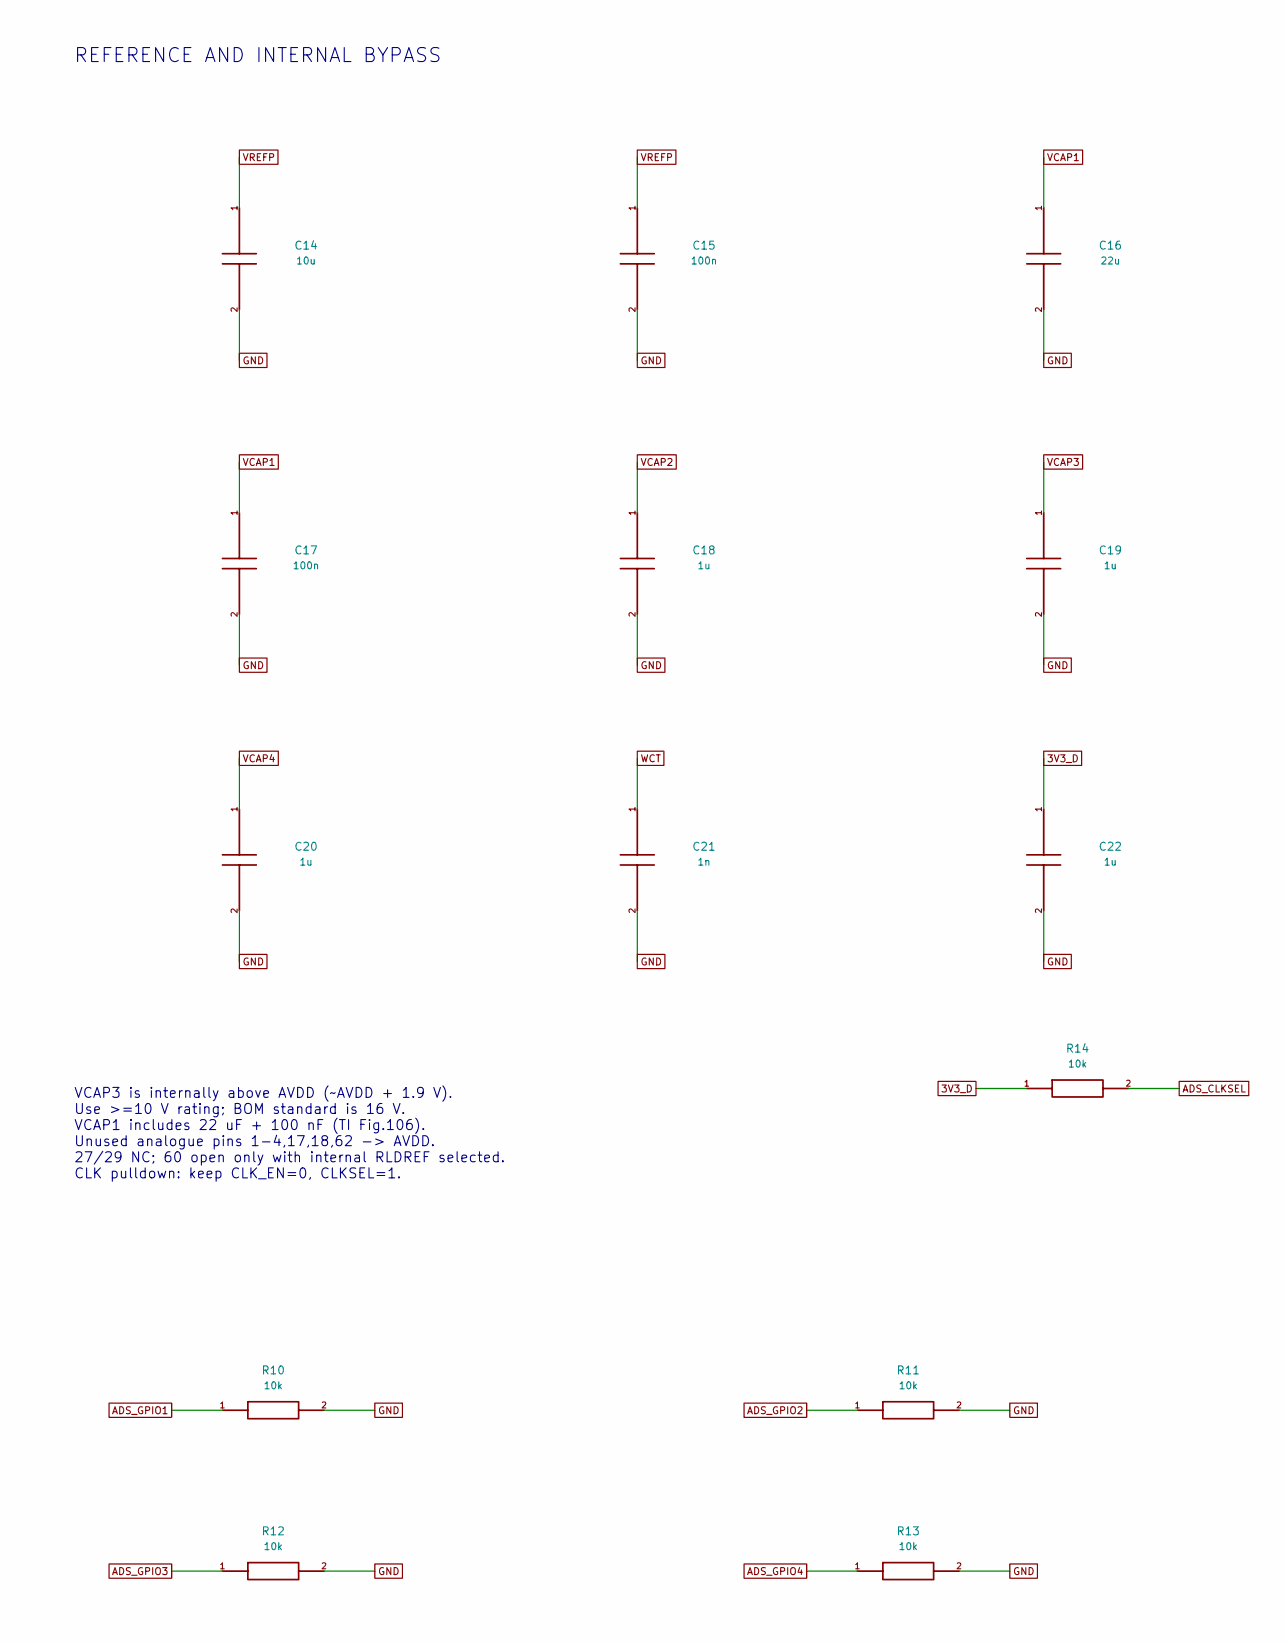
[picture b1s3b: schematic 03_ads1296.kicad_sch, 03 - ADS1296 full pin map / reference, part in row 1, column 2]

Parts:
C14: 10u; C_1206_3216Metric; MPN C1206C106K4PACTU
C15, C17: 100n; C_0805_2012Metric; MPN C0805C104K4RACTU
C16: 22u; C_1210_3225Metric; MPN C1210C226K4PACTU
C18, C19, C20, C22: 1u; C_0805_2012Metric; MPN C0805C105K4RACTU
C21: 1n; C_0805_2012Metric; MPN C0805C102J5GACTU
R10, R11, R12, R13, R14, R15: 10k; R_0805_2012Metric; MPN RC0805FR-0710KL
TP3: VREFP; TestPoint_Pad_D1.5mm
TP4: VCAP1; TestPoint_Pad_D1.5mm
TP5: ADS_DRDY_N; TestPoint_Pad_D1.5mm
U1: ADS1296IPAG; TQFP-64_10x10mm_P0.5mm; MPN ADS1296IPAG

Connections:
3V3_D: C22.1, R14.1, U1.48 (DVDD), U1.50 (DVDD); also elsewhere on the board
ADS_CLKSEL: R14.2, U1.52 (CLKSEL)
ADS_CLK_UNUSED: R15.1, U1.37 (CLK)
ADS_CS_N: U1.39 (~CS); also elsewhere on the board
ADS_DIN: U1.34 (DIN); also elsewhere on the board
ADS_DOUT: U1.43 (DOUT); also elsewhere on the board
ADS_DRDY_N: TP5.1, U1.47 (~DRDY); also elsewhere on the board
ADS_GPIO1: R10.1, U1.42 (GPIO1)
ADS_GPIO2: R11.1, U1.44 (GPIO2)
ADS_GPIO3: R12.1, U1.45 (GPIO3)
ADS_GPIO4: R13.1, U1.46 (GPIO4)
ADS_PWDN_N: U1.35 (~PWDN); also elsewhere on the board
ADS_RESET_N: U1.36 (~RESET); also elsewhere on the board
ADS_SCLK: U1.40 (SCLK); also elsewhere on the board
ADS_START: U1.38 (START); also elsewhere on the board
AVDD: U1.1 (IN8N_UNUSED), U1.2 (IN8P_UNUSED), U1.3 (IN7N_UNUSED), U1.4 (IN7P_UNUSED), U1.17 (TESTP_PACE1), U1.18 (TESTN_PACE2), U1.19 (AVDD), U1.21 (AVDD), U1.22 (AVDD), U1.54 (AVDD1), U1.56 (AVDD), U1.59 (AVDD), U1.62 (RLDIN); also elsewhere on the board
GND: C14.2, C15.2, C16.2, C17.2, C18.2, C19.2, C20.2, C21.2, C22.2, R10.2, R11.2, R12.2, R13.2, R15.2, U1.20 (AVSS), U1.23 (AVSS), U1.25 (VREFN), U1.31 (RESV1), U1.32 (AVSS), U1.33 (DGND), U1.41 (DAISY_IN), U1.49 (DGND), U1.51 (DGND), U1.53 (AVSS1), U1.57 (AVSS), U1.58 (AVSS); also elsewhere on the board
IN1N: U1.15 (IN1N); also elsewhere on the board
IN1P: U1.16 (IN1P); also elsewhere on the board
IN2N: U1.13 (IN2N); also elsewhere on the board
IN2P: U1.14 (IN2P); also elsewhere on the board
IN3N: U1.11 (IN3N); also elsewhere on the board
IN3P: U1.12 (IN3P); also elsewhere on the board
IN4N: U1.9 (IN4N); also elsewhere on the board
IN4P: U1.10 (IN4P); also elsewhere on the board
IN5N: U1.7 (IN5N); also elsewhere on the board
IN5P: U1.8 (IN5P); also elsewhere on the board
IN6N: U1.5 (IN6N); also elsewhere on the board
IN6P: U1.6 (IN6P); also elsewhere on the board
RLDINV: U1.61 (RLDINV); also elsewhere on the board
RLDOUT: U1.63 (RLDOUT); also elsewhere on the board
VCAP1: C16.1, C17.1, TP4.1, U1.28 (VCAP1)
VCAP2: C18.1, U1.30 (VCAP2)
VCAP3: C19.1, U1.55 (VCAP3)
VCAP4: C20.1, U1.26 (VCAP4)
VREFP: C14.1, C15.1, TP3.1, U1.24 (VREFP)
WCT: C21.1, U1.64 (WCT)

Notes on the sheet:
U1: TQFP-64 / 10 x 10 mm body / 0.5 mm pitch
REFERENCE AND INTERNAL BYPASS
VCAP3 is internally above AVDD (~AVDD + 1.9 V). Use >=10 V rating; BOM standard is 16 V. VCAP1 includes 22 uF + 100 nF (TI Fig.106). Unused analogue pins 1-4,17,18,62 -> AVDD. 27/29 NC; 60 open only with internal RLDREF selected. CLK pulldown: keep CLK_EN=0, CLKSEL=1.
PGA gain 6; internal 2.4 V reference; HR 4 kS/s. Disable external PACE/test outputs and WCT. Read 21 bytes/DRDY, SPI mode 1, 4 MHz. Reserve time for power-on, reference and filter settling.
